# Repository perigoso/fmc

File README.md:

# ipl motion controller

Flexible BLDC, Stepper, DC motor controller with position torque and speed control

## Authors

* **Rafael Silva** - [gimbas](https://github.com/crying-face-emoji)

See also the list of [contributors](https://github.com/gimbas/cp2130/graphs/contributors) who participated in this project.

## License

This project is licensed under the GNU General Public License v3.0 - see the [LICENSE.md](LICENSE.md) file for details

## Acknowledgments

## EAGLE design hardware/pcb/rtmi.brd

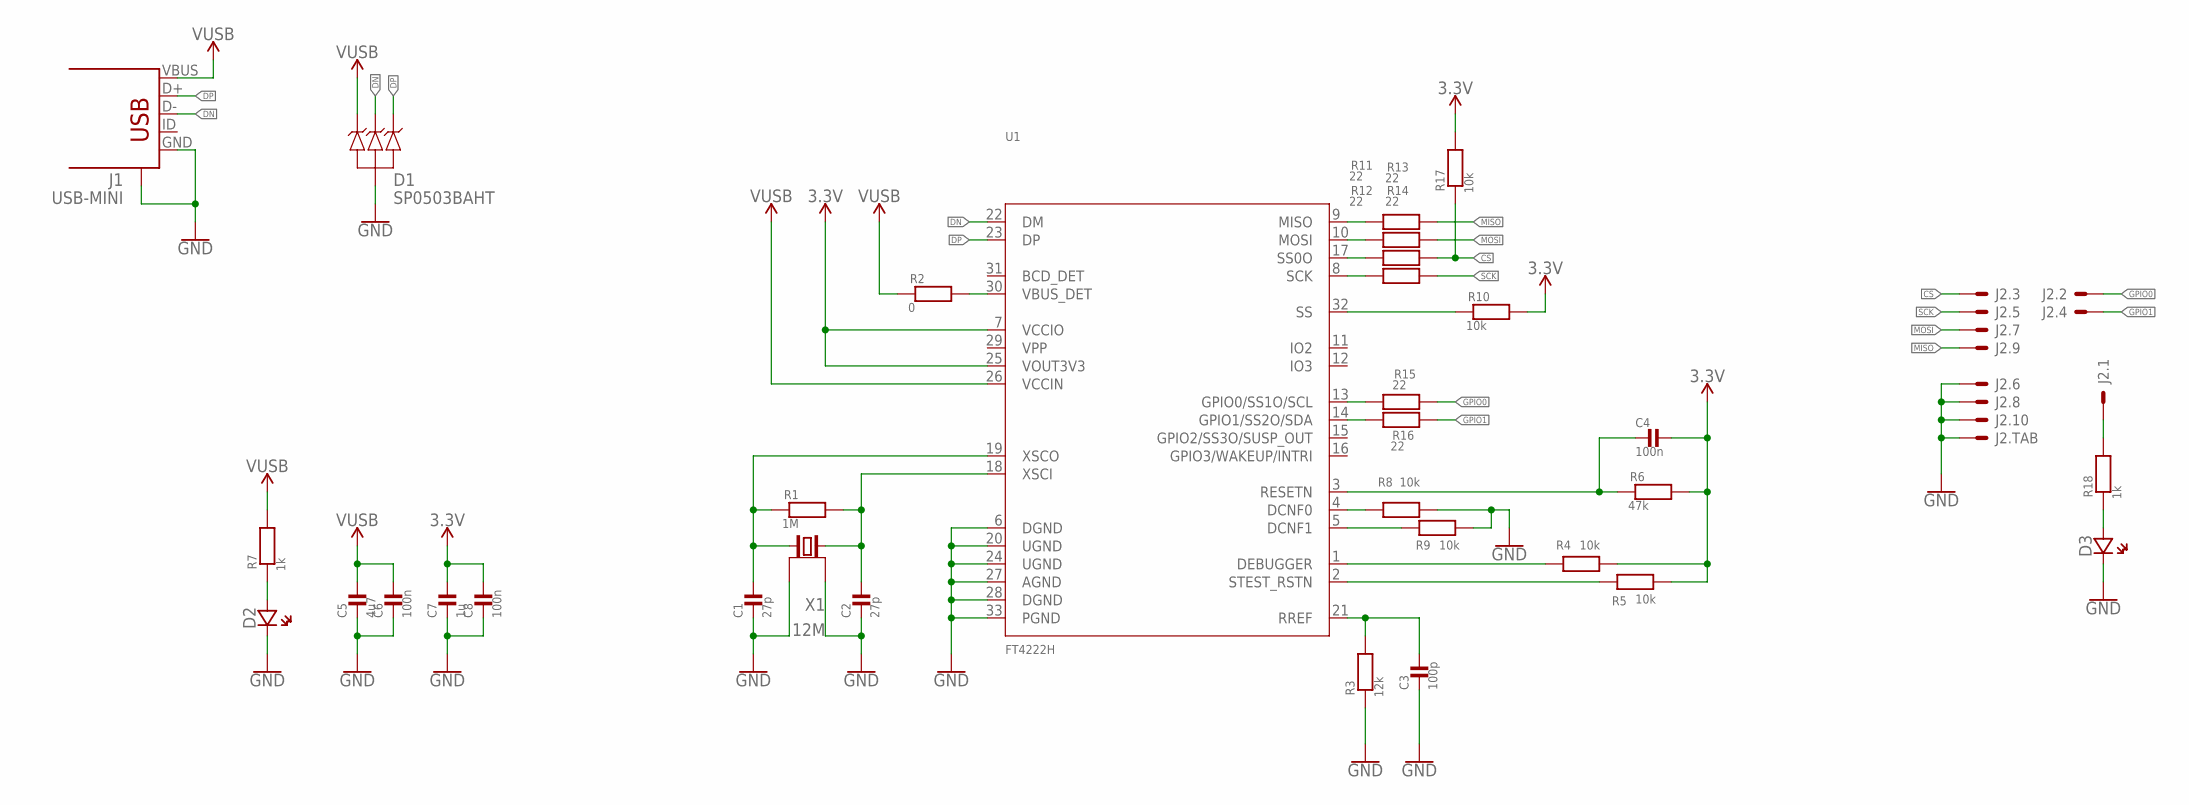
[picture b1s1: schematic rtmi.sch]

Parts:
C1, C2: 27p; 0603_WAVE
C3: 100p; 0603_WAVE
C4, C6, C8: 100n; 0603_WAVE
C5: 4u7; 0603_WAVE
C7: 1u; 0603_WAVE
D1: SP0503BAHT; SOT143
D2, D3: LED0603; CHIPLED_0603
J1: USB-MINI; USB-MINI-SMD
J2: F20F-10DP-1V
R1: 1M; 0603_WAVE
R2: 0; 0603_WAVE
R3: 12k; 0603_WAVE
R4, R5, R8, R9, R10, R17: 10k; 0603_WAVE
R6: 47k; 0603_WAVE
R7, R18: 1k; 0603_WAVE
R11, R12, R13, R14, R15, R16: 22; 0603_WAVE
U1: FT4222H; QFN32
X1: 12M; 4-SMD-3225

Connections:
3.3V: C4.P$1, C7.P$1, C8.P$1, R4.P$2, R5.P$2, R6.P$2, R10.P$2, R17.P$2, U1.7 (VCCIO), U1.25 (VOUT3V3)
3V3EXT: J2.1, R18.P$2
3V3EXT_LED: D3.A (AN), R18.P$1
CS: J2.3, R13.P$2, R17.P$1
DCFN1: R9.P$1, U1.5 (DCNF1)
DCNF0: R8.P$1, U1.4 (DCNF0)
DEBUGGER: R4.P$1, U1.1 (DEBUGGER)
DN: D1.3, J1.D-, U1.22 (DM)
DP: D1.4, J1.D+, U1.23 (DP)
GND: C1.P$2, C2.P$2, C3.P$2, C5.P$2, C6.P$2, C7.P$2, C8.P$2, D1.1, D2.C (CA), D3.C (CA), J1.GND, J1.GND@1 (CASE), J1.GND@2 (CASE), J1.GND@3 (CASE), J1.GND@4 (CASE), J2.6, J2.8, J2.10, J2.TAB1, J2.TAB2, R3.P$1, R8.P$2, R9.P$2, U1.6 (DGND), U1.20 (UGND), U1.24 (UGND), U1.27 (AGND), U1.28 (DGND), U1.33 (PGND), X1.2 (GND), X1.4 (GND)
GPIO0: J2.2, R15.P$2
GPIO0_PIN: R15.P$1, U1.13 (GPIO0/SS1O/SCL)
GPIO1: J2.4, R16.P$2
GPIO1_PIN: R16.P$1, U1.14 (GPIO1/SS2O/SDA)
MISO: J2.9, R11.P$2
MISO_PIN: R11.P$1, U1.9 (MISO)
MOSI: J2.7, R12.P$2
MOSI_PIN: R12.P$1, U1.10 (MOSI)
RESETN: C4.P$2, R6.P$1, U1.3 (RESETN)
RREF: C3.P$1, R3.P$2, U1.21 (RREF)
SCK: J2.5, R14.P$2
SCK_PIN: R14.P$1, U1.8 (SCK)
SS0O_PIN: R13.P$1, U1.17 (SS0O)
SS_PIN: R10.P$1, U1.32 (SS)
STEST_RSTN: R5.P$1, U1.2 (STEST_RSTN)
VBUS_DET: R2.P$2, U1.30 (VBUS_DET)
VUSB: C5.P$1, C6.P$1, D1.2, J1.VBUS, R2.P$1, R7.P$2, U1.26 (VCCIN)
VUSB_LED: D2.A (AN), R7.P$1
XSCI: C2.P$1, R1.P$2, U1.18 (XSCI), X1.1
XSCO: C1.P$1, R1.P$1, U1.19 (XSCO), X1.3 (2)

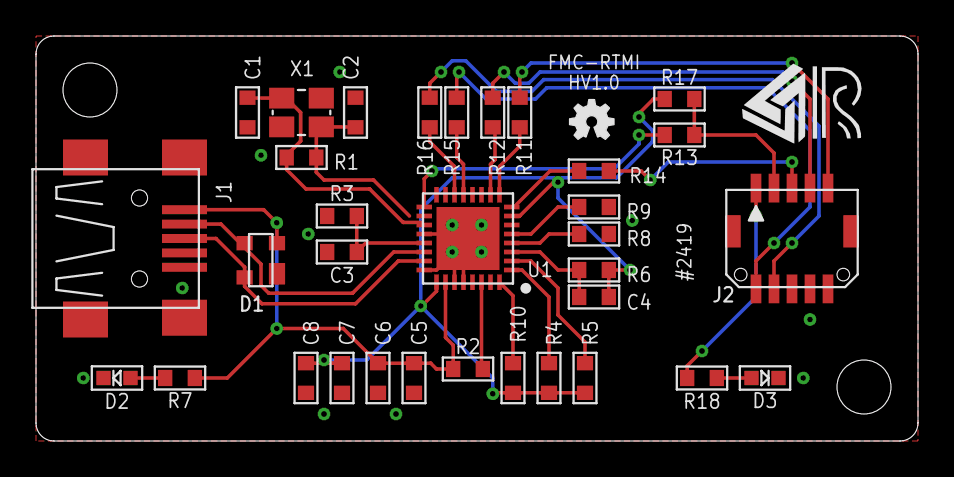
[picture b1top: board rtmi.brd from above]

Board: 2 copper layers, 49.0 x 22.5 mm, 36 parts (1 on the bottom side), 30 nets.

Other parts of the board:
U$1: OSHW-LOGO-M
U$2: OSHW-LOGO-MINI
U$4: RAFAEL_SILVA_5MM_ALT_3

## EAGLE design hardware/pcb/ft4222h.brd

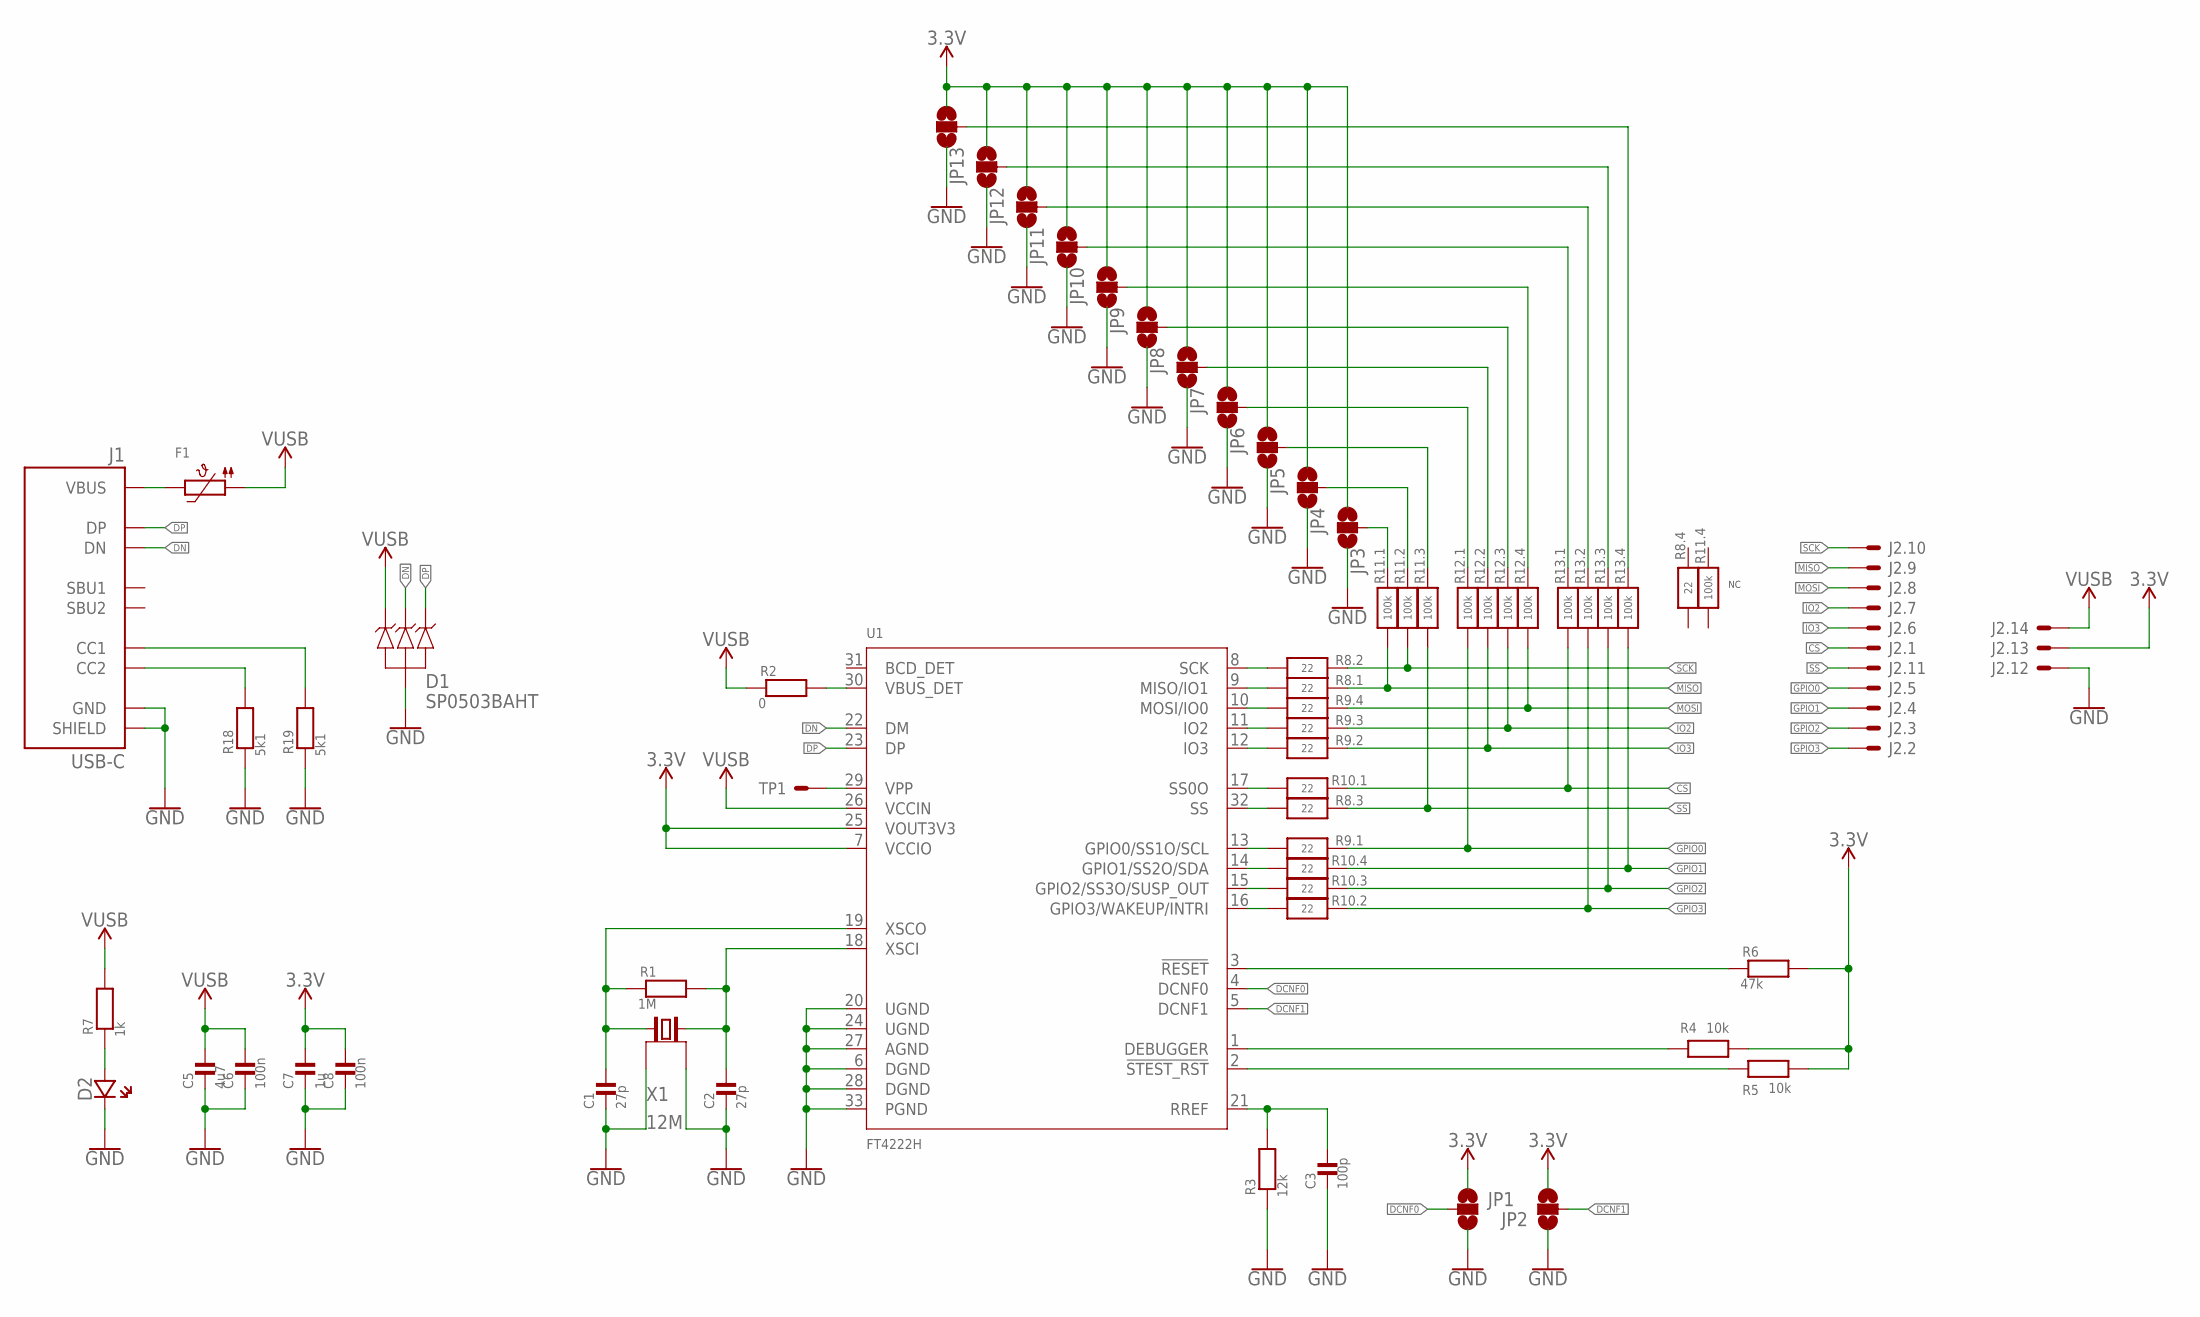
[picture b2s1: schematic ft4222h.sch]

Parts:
C1, C2: 27p; _0402
C3: 100p; _0402
C5: 4u7; 0603_WAVE
C6, C8: 100n; _0402
C7: 1u; 0603_WAVE
D1: SP0503BAHT; SOT143
D2: LED0603; CHIPLED_0603
F1: PTC0805; 0805
J1: USB-C
J2: 14; 2X7_2.54
JP1, JP2, JP3, JP4, JP5, JP6, JP7, JP8, JP9, JP10, JP11, JP12, JP13: JUMPER-SMT_3_NO_SILK; SMT-JUMPER_3_NO_SILK
R1: 1M; _0402
R2: 0; _0402
R3: 12k; _0402
R4, R5: 10k; _0402
R6: 47k; _0402
R7: 1k; _0402
R8, R9, R10: 22; RESPACK_4X0603
R11, R12, R13: 100k; RESPACK_4X0603
R18, R19: 5k1; _0402
TP1: TEST_POINT
U1: FT4222H; QFN32
X1: 12M; 4-SMD-3225

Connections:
3.3V: C7.P$1, C8.1, J2.13, JP1.1, JP2.3, JP3.3, JP4.3, JP5.3, JP6.3, JP7.3, JP8.3, JP9.3, JP10.3, JP11.3, JP12.3, JP13.3, R4.2, R5.2, R6.2, U1.7 (VCCIO), U1.25 (VOUT3V3)
CS: J2.1, R10.8 (2), R13.1
DCNF0: JP1.2, U1.4 (DCNF0)
DCNF1: JP2.2, U1.5 (DCNF1)
DEBUGGER: R4.1, U1.1 (DEBUGGER)
DN: D1.3, J1.A7 (DN), J1.B7 (DN), U1.22 (DM)
DP: D1.4, J1.A6 (DP), J1.B6 (DP), U1.23 (DP)
GND: C1.2, C2.2, C3.2, C5.P$2, C6.2, C7.P$2, C8.2, D1.1, D2.C (CA), J1.A1/B12 (GND), J1.B1/A12 (GND), J1.SHIELD0 (SHIELD), J1.SHIELD1 (SHIELD), J1.SHIELD2 (SHIELD), J1.SHIELD3 (SHIELD), J2.12, JP1.3, JP2.1, JP3.1, JP4.1, JP5.1, JP6.1, JP7.1, JP8.1, JP9.1, JP10.1, JP11.1, JP12.1, JP13.1, R3.1, R18.1, R19.1, U1.6 (DGND), U1.20 (UGND), U1.24 (UGND), U1.27 (AGND), U1.28 (DGND), U1.33 (PGND), X1.2 (GND), X1.4 (GND)
GPIO0: J2.5, R9.8 (2), R12.1
GPIO0_PIN: R9.1, U1.13 (GPIO0/SS1O/SCL)
GPIO0_PULL: JP6.2, R12.8 (2)
GPIO1: J2.4, R10.5 (2), R13.4 (1)
GPIO1_PIN: R10.4 (1), U1.14 (GPIO1/SS2O/SDA)
GPIO1_PULL: JP13.2, R13.5 (2)
GPIO2: J2.3, R10.6 (2), R13.3 (1)
GPIO2_PIN: R10.3 (1), U1.15 (GPIO2/SS3O/SUSP_OUT)
GPIO2_PULL: JP12.2, R13.6 (2)
GPIO3: J2.2, R10.7 (2), R13.2 (1)
GPIO3_PIN: R10.2 (1), U1.16 (GPIO3/WAKEUP/INTRI)
GPIO3_PULL: JP11.2, R13.7 (2)
IO2: J2.7, R9.6 (2), R12.3 (1)
IO2_PIN: R9.3 (1), U1.11 (IO2)
IO2_PULL: JP8.2, R12.6 (2)
IO3: J2.6, R9.7 (2), R12.2 (1)
IO3_PIN: R9.2 (1), U1.12 (IO3)
IO3_PULL: JP7.2, R12.7 (2)
MISO: J2.9, R8.8 (2), R11.1
MISO_PIN: R8.1, U1.9 (MISO/IO1)
MISO_PULL: JP3.2, R11.8 (2)
MOSI: J2.8, R9.5 (2), R12.4 (1)
MOSI_PIN: R9.4 (1), U1.10 (MOSI/IO0)
MOSI_PULL: JP9.2, R12.5 (2)
unnamed: J1.A5 (CC1), R19.2
unnamed: J1.B5 (CC2), R18.2
unnamed: F1.2, J1.A4/B9 (VBUS), J1.B4/A9 (VBUS)
unnamed: TP1.1, U1.29 (VPP)
RESETN: R6.1, U1.3 (!RESET)
RREF: C3.1, R3.2, U1.21 (RREF)
SCK: J2.10, R8.7 (2), R11.2 (1)
SCK_PIN: R8.2 (1), U1.8 (SCK)
SCK_PULL: JP4.2, R11.7 (2)
SS: J2.11, R8.6 (2), R11.3 (1)
SS0O_PIN: R10.1, U1.17 (SS0O)
SS0O_PULL: JP10.2, R13.8 (2)
SS_PIN: R8.3 (1), U1.32 (SS)
SS_PULL: JP5.2, R11.6 (2)
STEST_RSTN: R5.1, U1.2 (!STEST_RST)
VBUS_DET: R2.2, U1.30 (VBUS_DET)
VUSB: C5.P$1, C6.1, D1.2, F1.1, J2.14, R2.1, R7.2, U1.26 (VCCIN)
VUSB_LED: D2.A (AN), R7.1
XSCI: C2.1, R1.2, U1.18 (XSCI), X1.3 (2)
XSCO: C1.1, R1.1, U1.19 (XSCO), X1.1

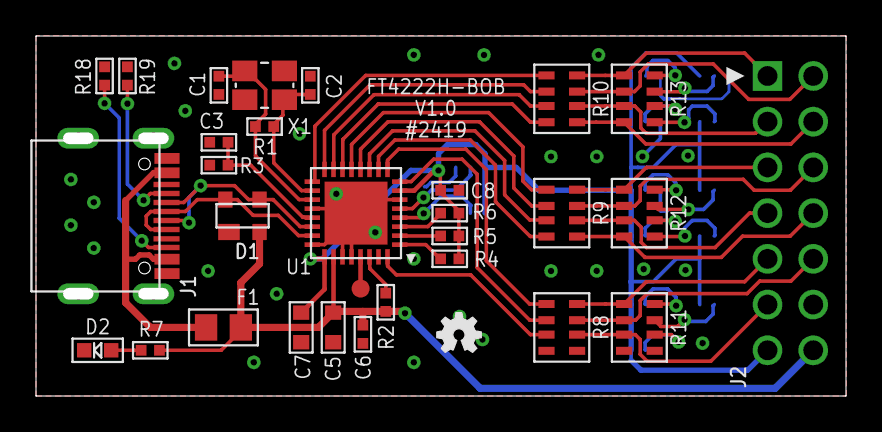
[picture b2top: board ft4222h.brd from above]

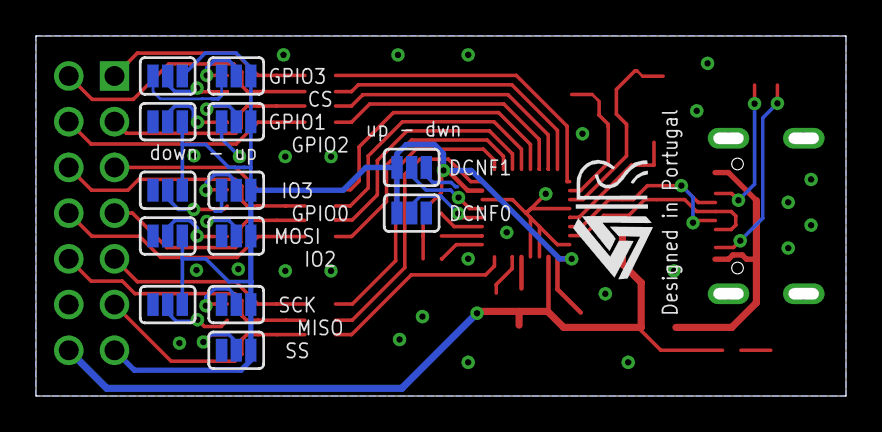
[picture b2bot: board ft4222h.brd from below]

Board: 2 copper layers, 45.0 x 20.0 mm, 45 parts (14 on the bottom side), 52 nets.

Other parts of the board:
U$1: OSHW-LOGO-MINI
U$2: RAFAEL_SILVA_5MM_ALT_3

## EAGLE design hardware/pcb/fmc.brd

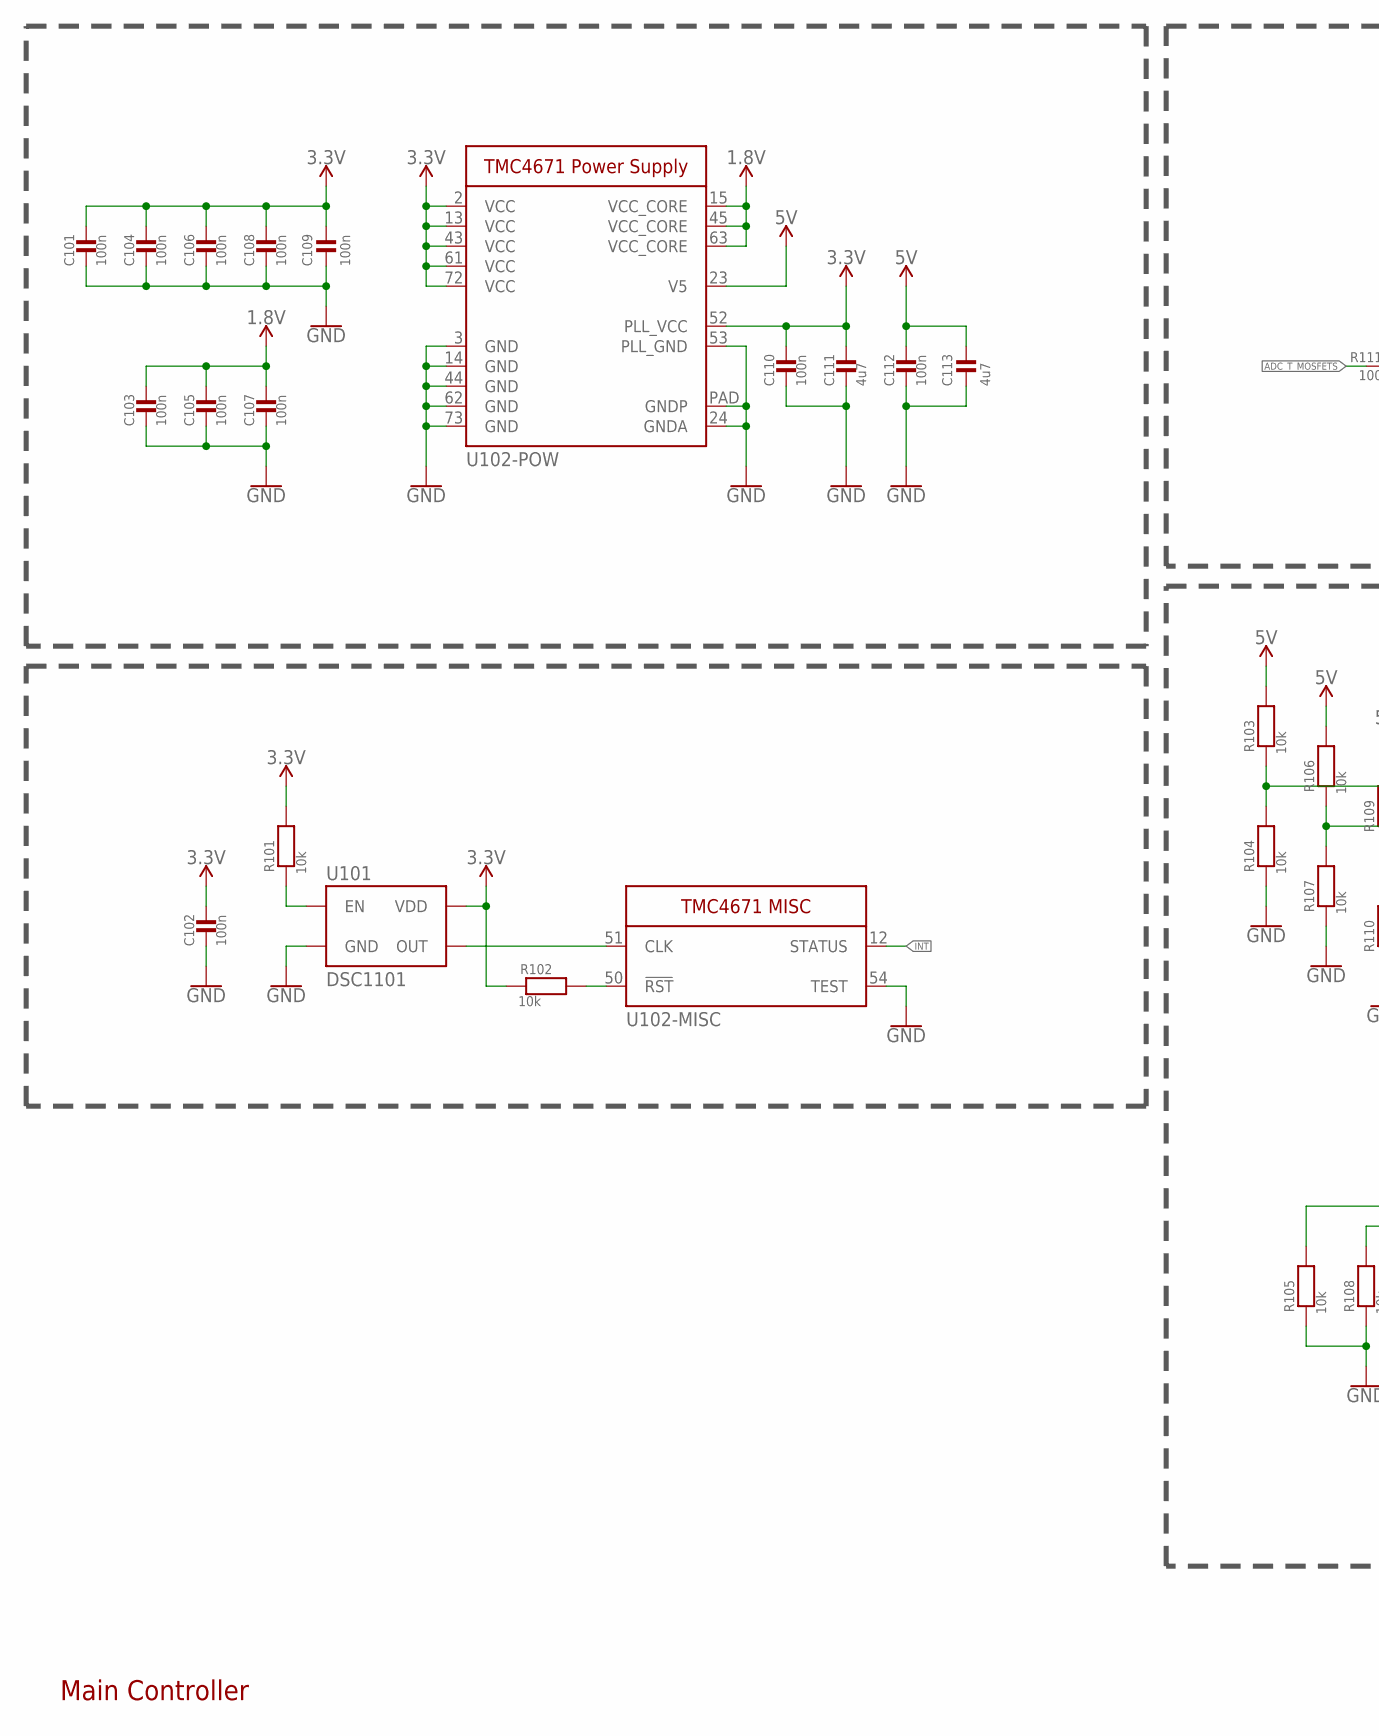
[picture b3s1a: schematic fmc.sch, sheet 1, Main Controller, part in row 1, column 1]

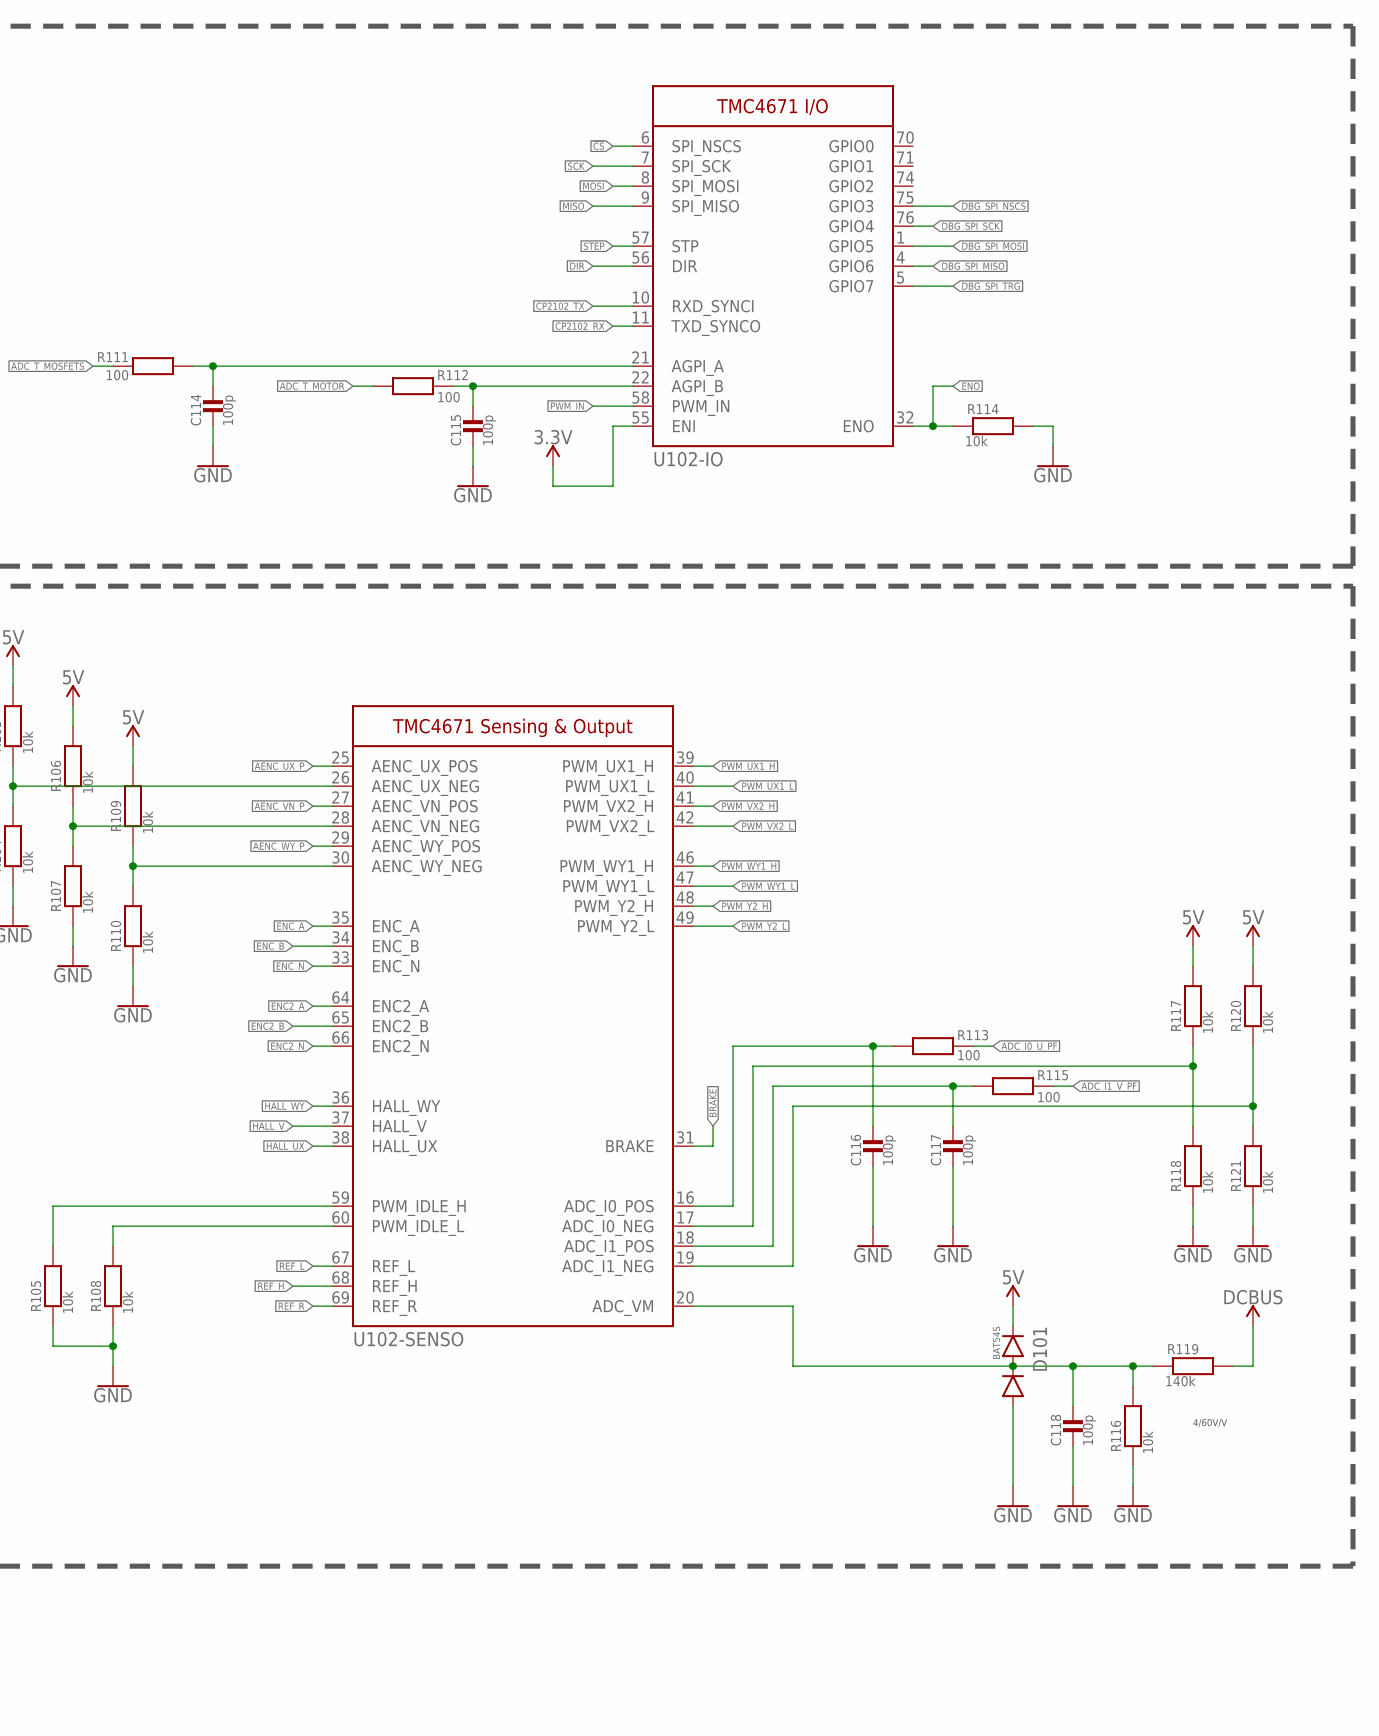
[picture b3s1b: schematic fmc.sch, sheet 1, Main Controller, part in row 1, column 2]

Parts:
C101, C102, C103, C104, C105, C106, C107, C108, C109, C110, C112: 100n; 0603_WAVE
C111, C113: 4u7; 0603_WAVE
C114, C115, C116, C117, C118: 100p; 0603_WAVE
D101: BAT54S; SOT-23-3
R101, R102, R103, R104, R105, R106, R107, R108, R109, R110, R114, R116, R117, R118, R120, R121: 10k; 0603_WAVE
R111, R112, R113, R115: 100; 0603_WAVE
R119: 140k; 0603_WAVE
U101: DSC1101; CDFN_5X3.2
U102: TMC4671; QFN76

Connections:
1.8V: C103.P$1, C105.P$1, C107.P$1, U102.15 (VCC_CORE), U102.45 (VCC_CORE), U102.63 (VCC_CORE)
3.3V: C101.P$1, C102.P$1, C104.P$1, C106.P$1, C108.P$1, C109.P$1, C110.P$1, C111.P$1, R101.P$2, R102.P$1, U101.6 (VDD), U102.2 (VCC), U102.13 (VCC), U102.43 (VCC), U102.52 (PLL_VCC), U102.55 (ENI), U102.61 (VCC), U102.72 (VCC); also elsewhere on the board
5V: C112.P$1, C113.P$1, D101.P$2 (2), R103.P$2, R106.P$2, R109.P$2, R117.P$2, R120.P$2, U102.23 (V5); also elsewhere on the board
!CS: U102.6 (SPI_NSCS); also elsewhere on the board
ADC_I0_U_PF: R113.P$2; also elsewhere on the board
ADC_I1_V_PF: R115.P$2; also elsewhere on the board
ADC_T_MOSFETS: R111.P$2; also elsewhere on the board
ADC_T_MOTOR: R112.P$1; also elsewhere on the board
AENC_UX_P: U102.25 (AENC_UX_POS); also elsewhere on the board
AENC_VN_P: U102.27 (AENC_VN_POS); also elsewhere on the board
AENC_WY_P: U102.29 (AENC_WY_POS); also elsewhere on the board
BRAKE: U102.31 (BRAKE); also elsewhere on the board
CP2102_RX: U102.11 (TXD_SYNCO); also elsewhere on the board
CP2102_TX: U102.10 (RXD_SYNCI); also elsewhere on the board
DBG_SPI_MISO: U102.4 (GPIO6); also elsewhere on the board
DBG_SPI_MOSI: U102.1 (GPIO5); also elsewhere on the board
DBG_SPI_NSCS: U102.75 (GPIO3); also elsewhere on the board
DBG_SPI_SCK: U102.76 (GPIO4); also elsewhere on the board
DBG_SPI_TRG: U102.5 (GPIO7); also elsewhere on the board
DCBUS: R119.P$2; also elsewhere on the board
DIR: U102.56 (DIR); also elsewhere on the board
ENC2_A: U102.64 (ENC2_A); also elsewhere on the board
ENC2_B: U102.65 (ENC2_B); also elsewhere on the board
ENC2_N: U102.66 (ENC2_N); also elsewhere on the board
ENC_A: U102.35 (ENC_A); also elsewhere on the board
ENC_B: U102.34 (ENC_B); also elsewhere on the board
ENC_N: U102.33 (ENC_N); also elsewhere on the board
ENO: R114.P$1, U102.32 (ENO); also elsewhere on the board
GND: C101.P$2, C102.P$2, C103.P$2, C104.P$2, C105.P$2, C106.P$2, C107.P$2, C108.P$2, C109.P$2, C110.P$2, C111.P$2, C112.P$2, C113.P$2, C114.P$2, C115.P$2, C116.P$2, C117.P$2, C118.P$2, D101.P$1 (1), R104.P$1, R105.P$1, R107.P$1, R108.P$1, R110.P$1, R114.P$2, R116.P$1, R118.P$1, R121.P$1, U101.3 (GND), U102.3 (GND), U102.14 (GND), U102.24 (GNDA), U102.44 (GND), U102.53 (PLL_GND), U102.54 (TEST), U102.62 (GND), U102.73 (GND), U102.PAD (GNDP); also elsewhere on the board
HALL_UX: U102.38 (HALL_UX); also elsewhere on the board
HALL_V: U102.37 (HALL_V); also elsewhere on the board
HALL_WY: U102.36 (HALL_WY); also elsewhere on the board
INT: U102.12 (STATUS); also elsewhere on the board
MISO: U102.9 (SPI_MISO); also elsewhere on the board
MOSI: U102.8 (SPI_MOSI); also elsewhere on the board
unnamed: C116.P$1, R113.P$1, U102.16 (ADC_I0_POS)
unnamed: R108.P$2, U102.60 (PWM_IDLE_L)
unnamed: R105.P$2, U102.59 (PWM_IDLE_H)
unnamed: U101.4 (OUT), U102.51 (CLK)
unnamed: R102.P$2, U102.50 (!RST!)
unnamed: R101.P$1, U101.1 (EN)
unnamed: C117.P$1, R115.P$1, U102.18 (ADC_I1_POS)
unnamed: R117.P$1, R118.P$2, U102.17 (ADC_I0_NEG)
unnamed: R120.P$1, R121.P$2, U102.19 (ADC_I1_NEG)
unnamed: C118.P$1, D101.P$3 (3), R116.P$2, R119.P$1, U102.20 (ADC_VM)
unnamed: C114.P$1, R111.P$1, U102.21 (AGPI_A)
unnamed: C115.P$1, R112.P$2, U102.22 (AGPI_B)
unnamed: R109.P$1, R110.P$2, U102.30 (AENC_WY_NEG)
unnamed: R106.P$1, R107.P$2, U102.28 (AENC_VN_NEG)
unnamed: R103.P$1, R104.P$2, U102.26 (AENC_UX_NEG)
PWM_IN: U102.58 (PWM_IN); also elsewhere on the board
PWM_UX1_H: U102.39 (PWM_UX1_H); also elsewhere on the board
PWM_UX1_L: U102.40 (PWM_UX1_L); also elsewhere on the board
PWM_VX2_H: U102.41 (PWM_VX2_H); also elsewhere on the board
PWM_VX2_L: U102.42 (PWM_VX2_L); also elsewhere on the board
PWM_WY1_H: U102.46 (PWM_WY1_H); also elsewhere on the board
PWM_WY1_L: U102.47 (PWM_WY1_L); also elsewhere on the board
PWM_Y2_H: U102.48 (PWM_Y2_H); also elsewhere on the board
PWM_Y2_L: U102.49 (PWM_Y2_L); also elsewhere on the board
REF_H: U102.68 (REF_H); also elsewhere on the board
REF_L: U102.67 (REF_L); also elsewhere on the board
REF_R: U102.69 (REF_R); also elsewhere on the board
SCK: U102.7 (SPI_SCK); also elsewhere on the board
STEP: U102.57 (STP); also elsewhere on the board

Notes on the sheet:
Main Controller
4/60V/V

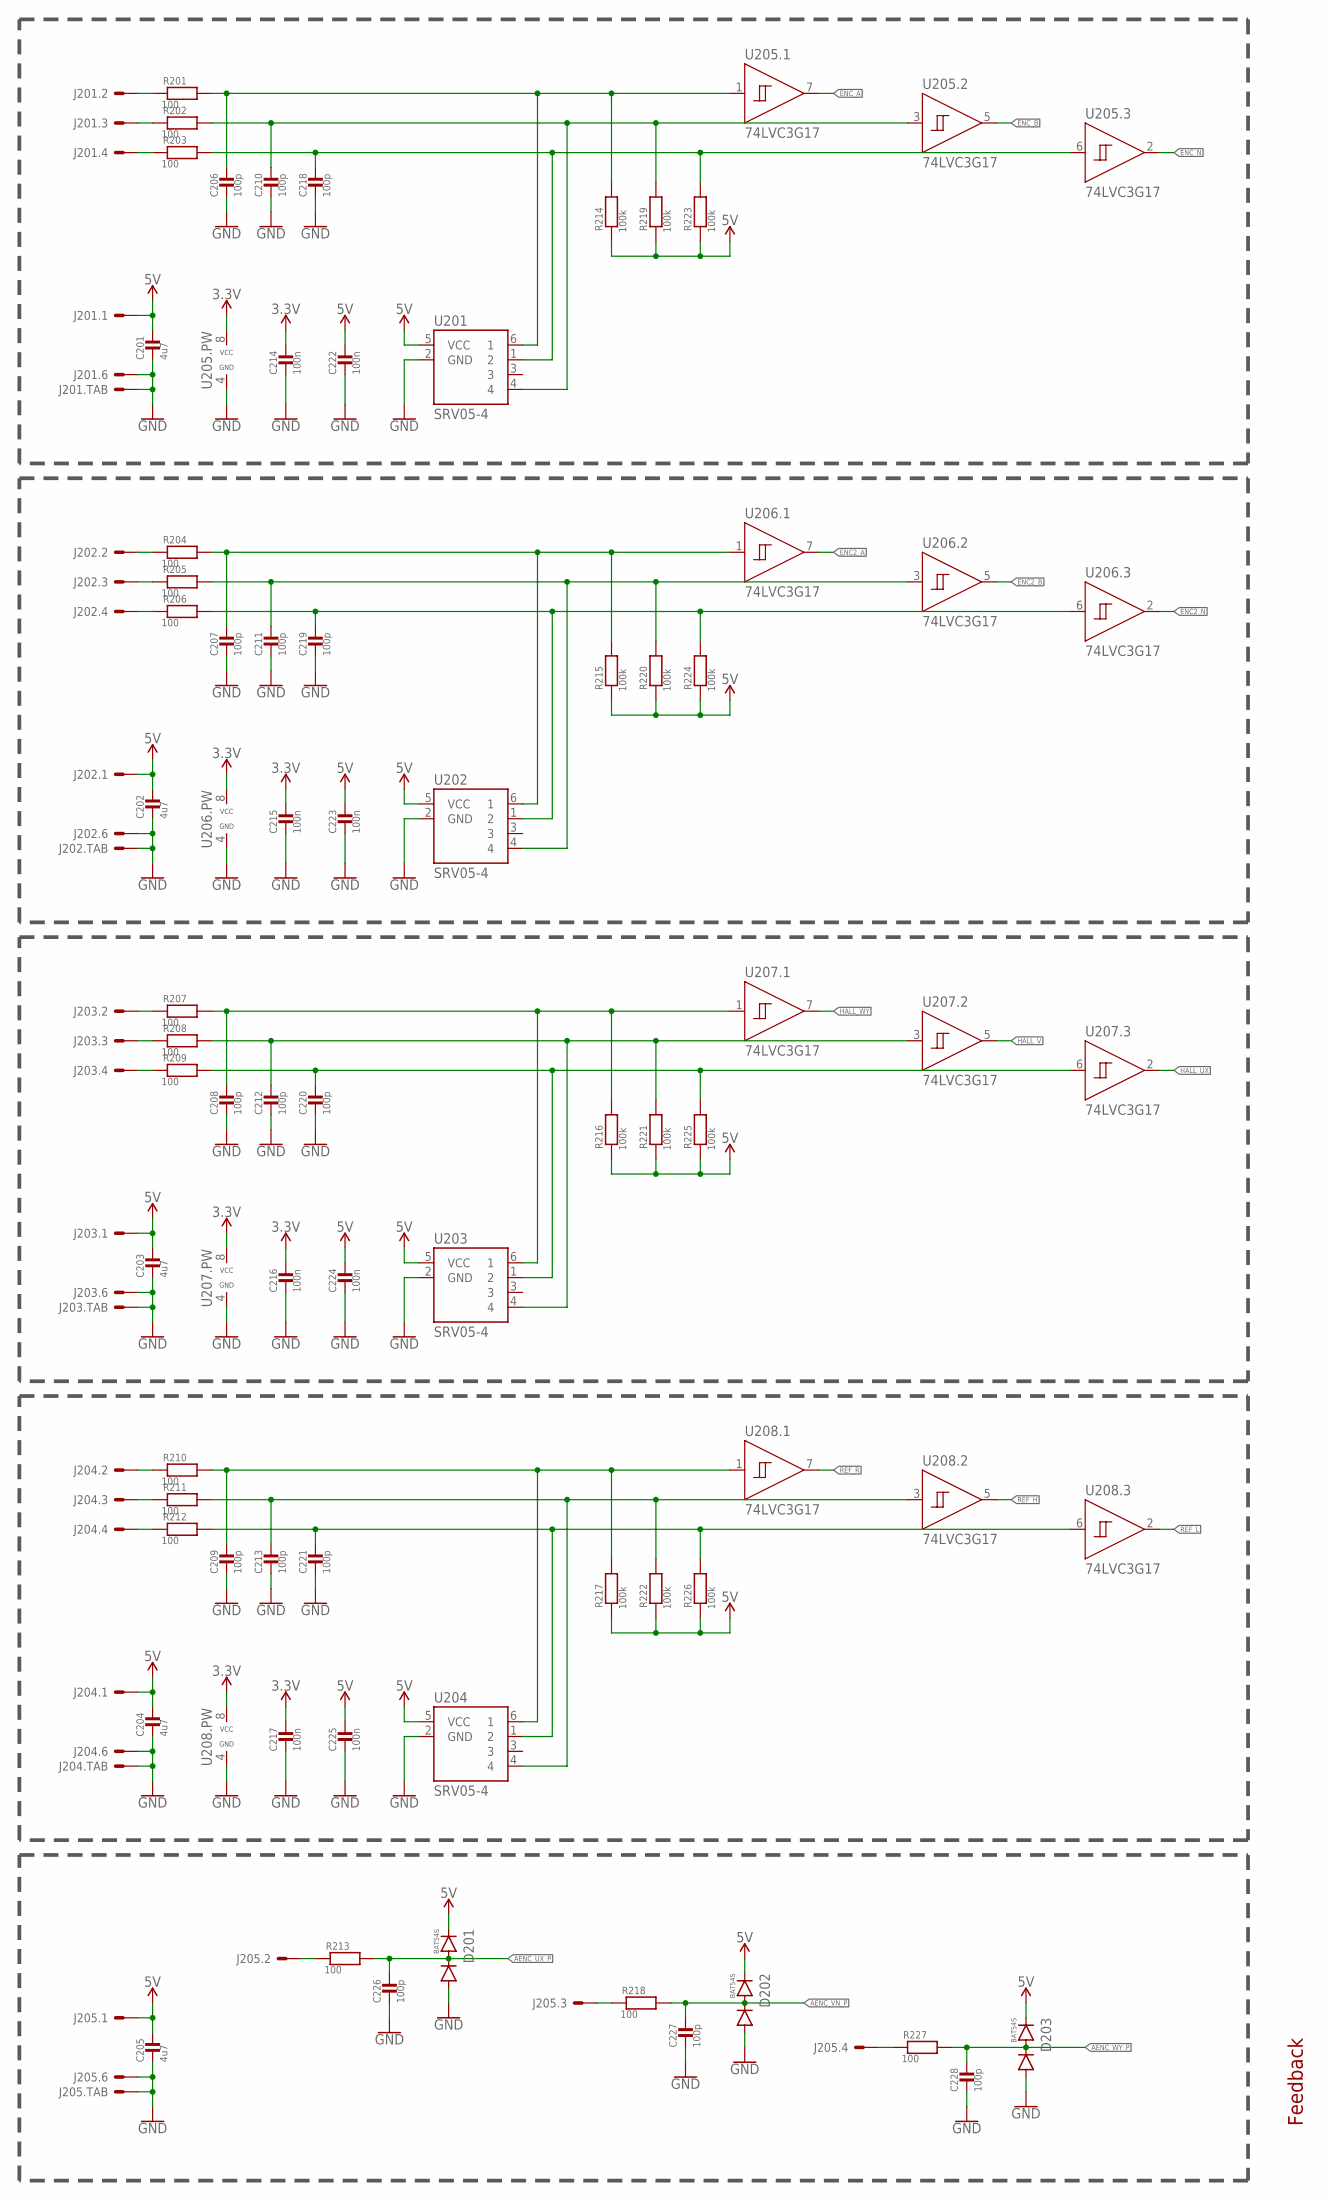
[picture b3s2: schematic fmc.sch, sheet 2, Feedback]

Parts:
C201, C202, C203, C204, C205: 4u7; 0603_WAVE
C206, C207, C208, C209, C210, C211, C212, C213, C218, C219, C220, C221, C226, C227, C228: 100p; 0603_WAVE
C214, C215, C216, C217, C222, C223, C224, C225: 100n; 0603_WAVE
D201, D202, D203: BAT54S; SOT-23-3
J201, J202, J203, J204, J205: SH-5; SM05B-SSR-H-TB
R201, R202, R203, R204, R205, R206, R207, R208, R209, R210, R211, R212, R213, R218, R227: 100; 0603_WAVE
R214, R215, R216, R217, R219, R220, R221, R222, R223, R224, R225, R226: 100k; 0603_WAVE
U201, U202, U203, U204: SRV05-4; SOT23-6
U205, U206, U207, U208: 74LVC3G17; TSSOP-8

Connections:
3.3V: C214.P$1, C215.P$1, C216.P$1, C217.P$1, U205.8 (VCC), U206.8 (VCC), U207.8 (VCC), U208.8 (VCC); also elsewhere on the board
5V: C201.P$1, C202.P$1, C203.P$1, C204.P$1, C205.P$1, C222.P$1, C223.P$1, C224.P$1, C225.P$1, D201.P$2 (2), D202.P$2 (2), D203.P$2 (2), J201.1, J202.1, J203.1, J204.1, J205.1, R214.P$1, R215.P$1, R216.P$1, R217.P$1, R219.P$1, R220.P$1, R221.P$1, R222.P$1, R223.P$1, R224.P$1, R225.P$1, R226.P$1, U201.5 (VCC), U202.5 (VCC), U203.5 (VCC), U204.5 (VCC); also elsewhere on the board
AENC_UX@J: J205.2, R213.P$1
AENC_UX_P: C226.P$1, D201.P$3 (3), R213.P$2; also elsewhere on the board
AENC_VN@J: J205.3, R218.P$1
AENC_VN_P: C227.P$1, D202.P$3 (3), R218.P$2; also elsewhere on the board
AENC_WY@J: J205.4, R227.P$1
AENC_WY_P: C228.P$1, D203.P$3 (3), R227.P$2; also elsewhere on the board
ENC2_A: U206.7 (Y); also elsewhere on the board
ENC2_B: U206.5 (Y); also elsewhere on the board
ENC2_N: U206.2 (Y); also elsewhere on the board
ENC_2_A@J: J202.2, R204.P$1
ENC_2_B@J: J202.3, R205.P$1
ENC_2_N@J: J202.4, R206.P$1
ENC_A: U205.7 (Y); also elsewhere on the board
ENC_A@J: J201.2, R201.P$1
ENC_B: U205.5 (Y); also elsewhere on the board
ENC_B@J: J201.3, R202.P$1
ENC_N: U205.2 (Y); also elsewhere on the board
ENC_N@J: J201.4, R203.P$1
GND: C201.P$2, C202.P$2, C203.P$2, C204.P$2, C205.P$2, C206.P$2, C207.P$2, C208.P$2, C209.P$2, C210.P$2, C211.P$2, C212.P$2, C213.P$2, C214.P$2, C215.P$2, C216.P$2, C217.P$2, C218.P$2, C219.P$2, C220.P$2, C221.P$2, C222.P$2, C223.P$2, C224.P$2, C225.P$2, C226.P$2, C227.P$2, C228.P$2, D201.P$1 (1), D202.P$1 (1), D203.P$1 (1), J201.5, J201.FIT@1, J201.FIT@2, J202.5, J202.FIT@1, J202.FIT@2, J203.5, J203.FIT@1, J203.FIT@2, J204.5, J204.FIT@1, J204.FIT@2, J205.5, J205.FIT@1, J205.FIT@2, U201.2 (GND), U202.2 (GND), U203.2 (GND), U204.2 (GND), U205.4 (GND), U206.4 (GND), U207.4 (GND), U208.4 (GND); also elsewhere on the board
HALL_UX: U207.2 (Y); also elsewhere on the board
HALL_UX@J: J203.4, R209.P$1
HALL_V: U207.5 (Y); also elsewhere on the board
HALL_V@J: J203.3, R208.P$1
HALL_WY: U207.7 (Y); also elsewhere on the board
HALL_WY@J: J203.2, R207.P$1
unnamed: C218.P$1, R203.P$2, R223.P$2, U201.1 (2), U205.6 (A)
unnamed: C210.P$1, R202.P$2, R219.P$2, U201.4, U205.3 (A)
unnamed: C219.P$1, R206.P$2, R224.P$2, U202.1 (2), U206.6 (A)
unnamed: C206.P$1, R201.P$2, R214.P$2, U201.6 (1), U205.1 (A)
unnamed: C211.P$1, R205.P$2, R220.P$2, U202.4, U206.3 (A)
unnamed: C207.P$1, R204.P$2, R215.P$2, U202.6 (1), U206.1 (A)
unnamed: C220.P$1, R209.P$2, R225.P$2, U203.1 (2), U207.6 (A)
unnamed: C212.P$1, R208.P$2, R221.P$2, U203.4, U207.3 (A)
unnamed: C208.P$1, R207.P$2, R216.P$2, U203.6 (1), U207.1 (A)
unnamed: C221.P$1, R212.P$2, R226.P$2, U204.1 (2), U208.6 (A)
unnamed: C213.P$1, R211.P$2, R222.P$2, U204.4, U208.3 (A)
unnamed: C209.P$1, R210.P$2, R217.P$2, U204.6 (1), U208.1 (A)
REF_H: U208.5 (Y); also elsewhere on the board
REF_H@J: J204.3, R211.P$1
REF_L: U208.2 (Y); also elsewhere on the board
REF_L@J: J204.4, R212.P$1
REF_R: U208.7 (Y); also elsewhere on the board
REF_R@J: J204.2, R210.P$1

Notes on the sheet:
Feedback

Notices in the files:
hardware/pcb/ft4222h.sch:
LICENSE: GNU General Public License v3.0
parts and their libraries:
Utility: Released under the Creative Commons
Utility: https://creativecommons.org/licenses/by-sa/4.0
